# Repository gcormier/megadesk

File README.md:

# megadesk
Do you wish your IKEA Bekant had memory buttons? I sure did. So I made megadesk. Design goals were to have it fit in the original housing and use as many stock parts as possible, be completely independant of the existing controller, as well as store any number of memory positions.

You can now use the [megadesk companion](https://www.tindie.com/products/gcormier/megadesk-companion/) if you want to integrate it with your smarthome.

# For sale on Tindie - Plug and Play!
I've setup a store on Tindie for those who wish to order a ready to go, plug and play version. It comes with a fully assembled PCB as well as the cable you will need to connect it. No soldering or assembly required! <a  href="https://www.tindie.com/products/gcormier/megadesk/">https://www.tindie.com/products/gcormier/megadesk/</a>

## Features

### Recalibration
The factory recalibration routine has been implemented. The original BEKANT controller is no longer needed to recalibrate motors.
**This will cause the desk to move to the lowest possible extremity. Please exercise caution and be prepared to unplug the power if needed.**
Any interruption to this procedure requires a power-cycle.

### Serial control 
Enables serial input/output for what the megadesk is doing and to send commands. Some people wanted to have a smart/connected megadesk, but due to the size limitations of the space inside the case, an external module is the best solution. A lot of discussion in PR #12 and PR #58, as well as [discussion thread #87](https://github.com/gcormier/megadesk/discussions/87). 

You should also check out [Megadesk Companion](https://github.com/gcormier/megadesk_companion) for a plug and play `esphome` solution.

More information in [Serial.md](Serial.md). There's also specific details on [esphome](esphome.md).

### Custom MIN/MAX
Enabled by default, no limits.

This allows you to specify custom values for the minimum and maximum height of your desk. This is useful if you have things stored underneath, or maximum height limitations (shelf on the wall).

- Memory 11 will use the current desk height to set the minimum limit. If already set, it will clear it.
- Memory 12 will use the current desk height to set the maximum limit. If already set, it will clear it.

### Audio Feedback
Disabled by default.

Adds extra audio feedback when pushing buttons or using functions.

### Dual-button memory
Disabled by default.

This allows storing unique memory positions against each button. When enabled, you could save a double-click position for the up button as well a double-click position for the down button.

# Disassembly of the existing control unit
I now have a <a href="https://www.youtube.com/watch?v=jCPlM2KYwDQ">video with a few tips</a> on disassembling the IKEA Bekant controller and installing megadesk. Due to popular request, I now have a <a href="https://www.youtube.com/watch?v=qiOev3miDo8">second video with live surgery</a> of a brand new, unopened control unit.

**NOTE:** While the recalibration feature has been added to megadesk, it is recommended to keep your original board.

## Video
Unfortunately the beeps aren't captured well in the video unless you turn up the volume.

# Quick Commands
| UP pushes | Function | Audio Feedback
| --------- | -------- | --------
| 2-10      | Memory positions | # of beeps + high tone (saving), # of beeps (recall), # of beeps + sad tone (recall, no memory saved at that location)
| 11        | Set the lowest/minimum height to current position, or, reset back to default (toggles) | 4 low beeps when setting a limit. Single low beep - disabled.
| 12        | Set the highest/maximum height to current position, or, reset back to default (toggles) | 4 high beeps when setting a limit. Single high beep - disabled.
| 14        | Recalibration procedure, desk will lower down to the lowest limits | (Will begin moving)
| 15        | Reset | Fanfare
| 16        | Newer units, no operation. Units before Feb 2021 - toggle different variants.
| 17        | Toggle audio-feedback mode | double beep enabled. single beep disabled.
| 18        | Toggle both-button mode | double beep enabled. single beep disabled.

# Setting and Recalling memory slots
## Setting
To set assign a memory slot you press the up button two or more times. On the final button press you hold until you hear a tone that indicates what slot you have assigned (2 beeps, 3 beeps, etc).

## Recalling
To recall a memory slot you push the up button the number of times for that memory slot (2 for first slot, 3 for second slot, etc). If you try to recall a memory slot that has not been saved you will hear an "error" chime indicating that no height information could be recalled.

# Troubleshooting
1. Have you tried turning it off again? :)
    - Seriously - from testing many of these units, about 1 out of 20 times the handshake seems to fail as it does contain some random elements. A simple power cycle will provide a new handshake and the unit will power up.
    - Try unplugging the desk from the wall and plugging it back in (With megadesk connected)
    - Alternatively, try powering on the desk with NO controller attached, and then plugging in the megadesk after the desk is powered on.
    - Note that the power supply that comes with the BEKANT can store a charge for quite some time. It might be necessary to leave it unplugged for 60-120 seconds for it to lose that charge.
1. Is the safety key inserted? It is still required for the motors to engage. You will not hear any beeps when using buttons if it is removed.
1. Try different variant modes described above by pushing UP 16 times. (Pre Feb-2021 units only)
1. Test the buttons
    - Holding DOWN while powering on will wipe the EEPROM and enter a button test mode, where the up/down buttons can be held to test that they are working - a power cycle is required to exit this mode.
    - If they don't work
        - Ensure the safety key is fully inserted
        - Ensure the ribbon cable is seated far enough
        - If the FPC connector has a latch, ensure it is [latched](https://www.youtube.com/shorts/f_H-t_oJuzk)
        - You can clean the ribbon cable gently with a swab and rubbing alcohol which has been [reported to help](https://github.com/gcormier/megadesk/discussions/114) with intermittent issues
1. Factory Reset
    - Holding DOWN while powering on will wipe the EEPROM and enter a button test mode (see above) - a power cycle is required to exit this mode.
1. Recalibrate/reset the motors
   1. Factory controller
      - This step must be done with the **ORIGINAL** BEKANT controller.
      - Hold the UP and DOWN buttons for 8 seconds, after that let go of up while maintaining the pressure on the down button.
      - The desk will lower until it stops on its own.
      - Let go of all buttons, and test regular desk functionality with the original controller.
      - Once functionality is confirmed, replace with megadesk.   
   1. Megadesk
      - Push the UP button 14 times. 

# In the news
If you've made a blog/video posting with Megadesk, please open a PR to add it here, or send me a message with the URL.
1. https://calvin.me/ikea-bekant-megadesk/
1. https://www.youtube.com/watch?v=QopaeB1k6LU

# Hacking, contributing and DIY
This has been moved to [DIY.md](DIY.md) 

# esphome configuration
esphome example configuration avalible at [esphome.md](esphome.md), and other sample configurations in [esphome folder](https://github.com/gcormier/megadesk/tree/master/esphome)

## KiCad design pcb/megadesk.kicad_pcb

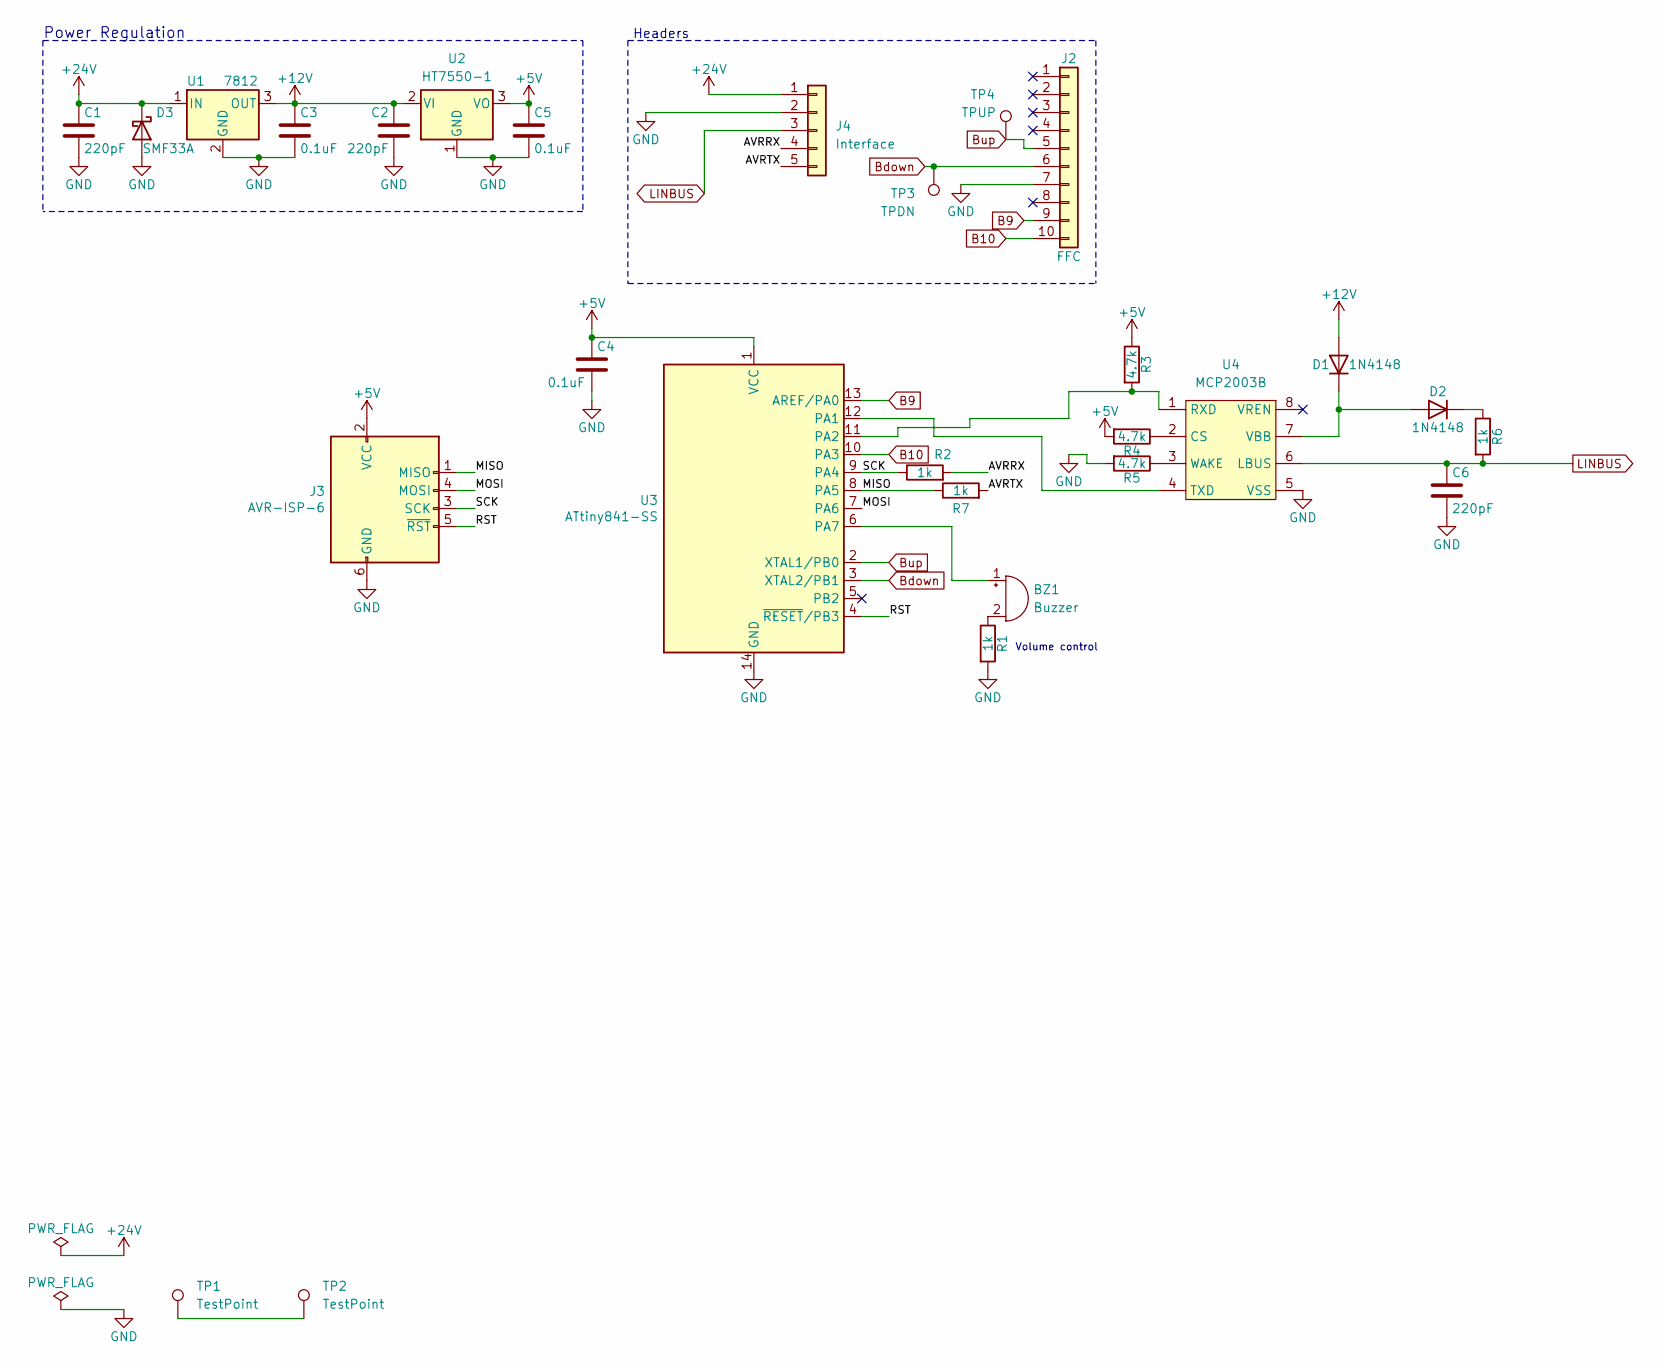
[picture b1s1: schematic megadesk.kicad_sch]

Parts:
BZ1: Buzzer; Buzzer_Murata_PKMCS0909E; Part Number PKMCS0909E4000-R1; LCSC C391035
C1, C2, C6: 220pF; C_0603_1608Metric; LCSC C1603
C3, C4, C5: 0.1uF; C_0805_2012Metric; LCSC C49678
D1, D2: 1N4148; D_SOD-323; Part Number 1N4148WSFSCT; LCSC C2128
D3: SMF33A; D_SOD-123F; LCSC C353288
J2: FFC; F1004-H-10-20G-R; Part Number A100308TR-ND; LCSC C668117
J3: AVR-ISP-6; PinHeader_2x03_P2.54mm_Vertical; Part Number DNP; LCSC DNP
J4: Interface; PinHeader_1x05_P2.54mm_Horizontal; LCSC C492413
R1, R2, R6, R7: 1k; R_0603_1608Metric; LCSC C21190
R3, R4, R5: 4.7k; R_0603_1608Metric; LCSC C23162
TP1, TP2: TestPoint; TestPoint_Pad_D1.5mm
TP3: TPDN; TestPoint_Pad_D1.5mm
TP4: TPUP; TestPoint_Pad_D1.5mm
U1: 7812; TO-252-2; Part Number 7812; LCSC C116325
U2: HT7550-1; SOT-89-3; LCSC C16106
U3: ATtiny841-SS; SOIC-14_3.9x8.7mm_P1.27mm; Part Number ATTINY841-SSUR; LCSC C614879
U4: MCP2003B; SOIC-8_3.9x4.9mm_P1.27mm; LCSC C152207

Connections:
+5V: C4.1, C5.1, J3.2 (VCC), R3.1, R4.2, U2.3 (VO), U3.1 (VCC)
+12V: C2.1, C3.1, D1.2 (A), U1.3 (OUT), U2.2 (VI)
+24V: C1.1, D3.1 (K), J4.1, U1.1 (IN)
/AVRRX: J4.4, R2.2
/AVRTX: J4.5, R7.2
/MISO: J3.1 (MISO), R7.1, U3.8 (PA5)
/MOSI: J3.4 (MOSI), U3.7 (PA6)
/RST: J3.5 (~RST), U3.4 (~RESET/PB3)
/SCK: J3.3 (SCK), R2.1, U3.9 (PA4)
B9: J2.9, U3.13 (AREF/PA0)
B10: J2.10, U3.10 (PA3)
Bdown: J2.6, TP3.1, U3.3 (XTAL2/PB1)
Bup: J2.5, TP4.1, U3.2 (XTAL1/PB0)
GND: C1.2, C2.2, C3.2, C4.2, C5.2, C6.2, D3.2 (A), J2.7, J3.6 (GND), J4.2, R1.2, R5.2, U1.2 (GND), U2.1 (GND), U3.14 (GND), U4.5 (VSS)
LINBUS: C6.1, J4.3, R6.2, U4.6 (LBUS)
unnamed: BZ1.2 (+), R1.1
unnamed: BZ1.1 (-), U3.6 (PA7)
unnamed: D1.1 (K), D2.2 (A), U4.7 (VBB)
unnamed: D2.1 (K), R6.1
unnamed: TP1.1, TP2.1
unnamed: U3.12 (PA1), U4.4 (TXD)
unnamed: R3.2, U3.11 (PA2), U4.1 (RXD)
unnamed: R4.1, U4.2 (CS)
unnamed: R5.1, U4.3 (WAKE)

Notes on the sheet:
Power Regulation
Headers
Volume control

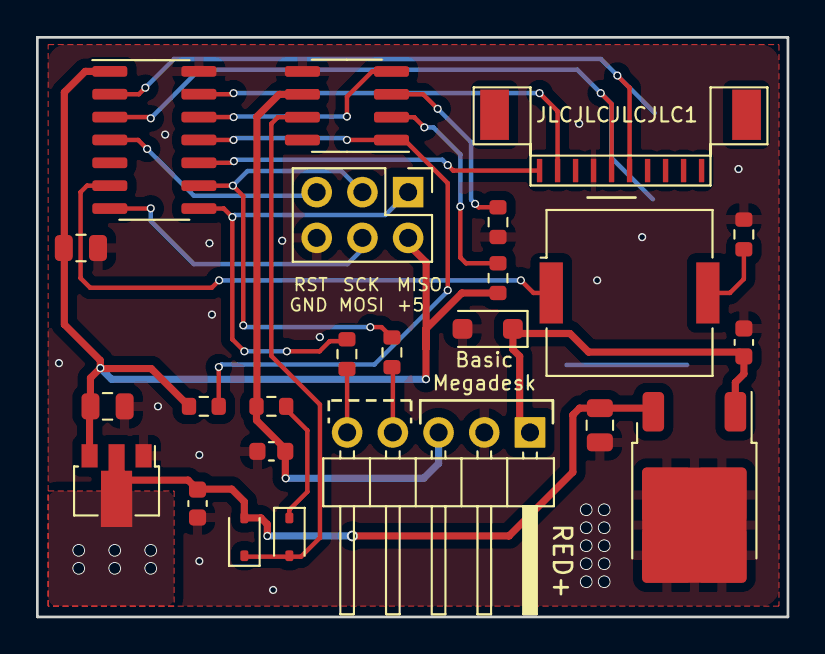
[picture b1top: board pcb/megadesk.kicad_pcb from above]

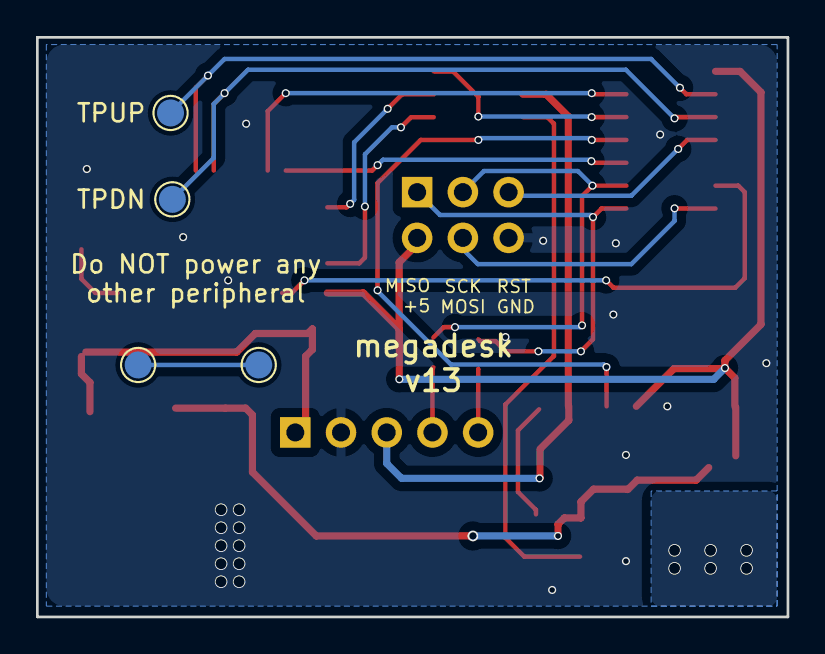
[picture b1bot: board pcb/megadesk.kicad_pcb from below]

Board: 2 copper layers, 41.7 x 32.2 mm, 28 parts (4 on the bottom side), 24 nets.

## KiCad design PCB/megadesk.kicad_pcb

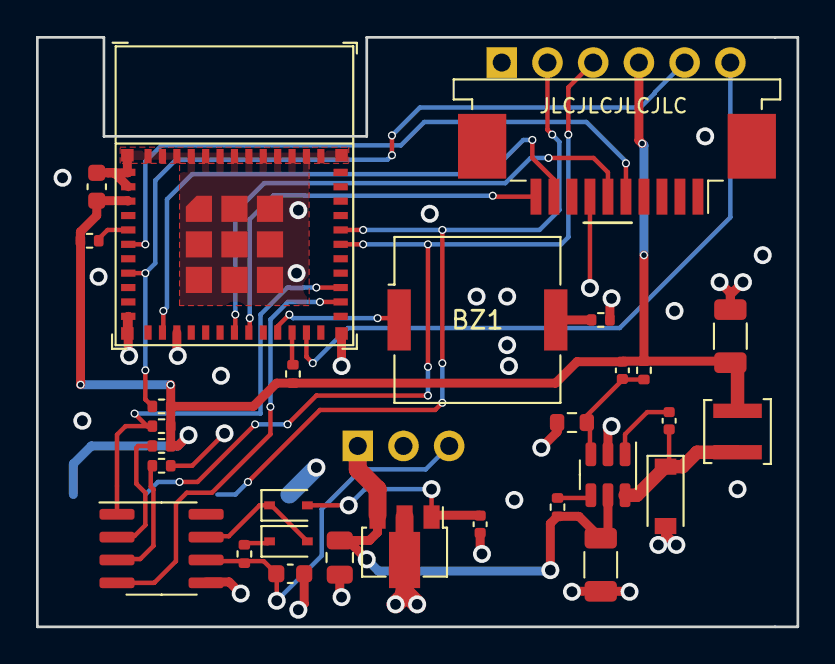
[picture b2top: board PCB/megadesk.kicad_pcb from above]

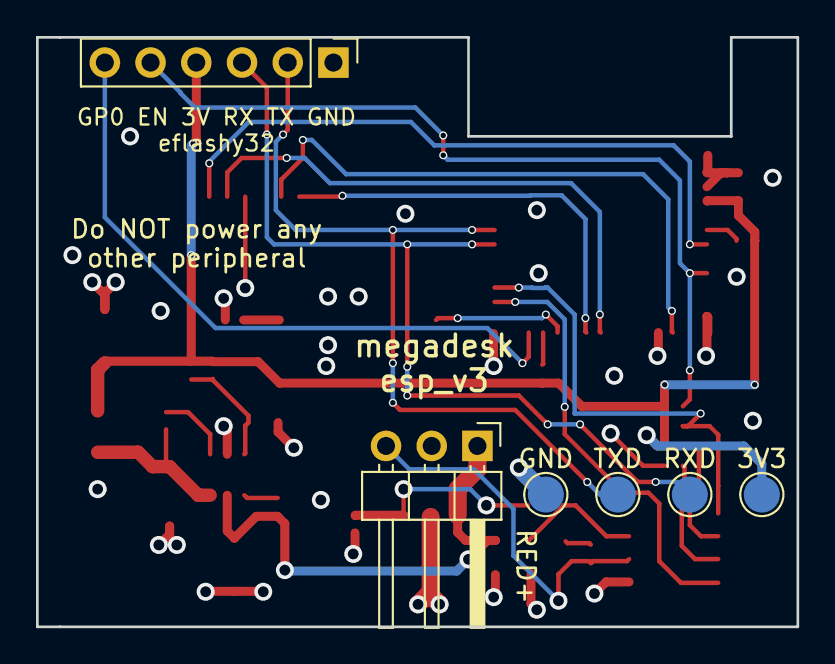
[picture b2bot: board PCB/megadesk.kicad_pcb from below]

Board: 4 copper layers, 42.2 x 32.8 mm, 35 parts (6 on the bottom side), 27 nets.

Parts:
BZ1: Buzzer; Buzzer_Murata_PKMCS0909E
C1: 0.33uF; C_0805_2012Metric
C3: 0.1uF; C_0402_1005Metric
C4: 10uF; C_0603_1608Metric
C6: 220pF; C_0603_1608Metric
C7: 4.7uF (50V); C_1206_3216Metric
C8: 0.1uF (50V); C_0402_1005Metric
C9: 33pF; C_0402_1005Metric
C10: 10uF (50V); C_1206_3216Metric
D1, D2: 1N4148; D_SOD-323
D4: 40V/1A; D_SOD-123
J1: Interface; PinHeader_1x03_P2.54mm_Horizontal
J2: FFC; TE_1-84953-0_1x10-1MP_P1.0mm_Horizontal
J3: eflashy32; PinHeader_1x06_P2.54mm_Vertical
L2: 2.2uH; L_Sunlord_SWPA3015S
R1, R6, R8: 1k; R_0402_1005Metric
R2, R7, R11: 10k; R_0402_1005Metric
R3, R4, R5: 4.7k; R_0402_1005Metric
R9: 40.2k; R_0603_1608Metric
R10: 124k; R_0402_1005Metric
TP1: RXD; TestPoint_Pad_D2.0mm
TP2: TXD; TestPoint_Pad_D2.0mm
TP3: GND; TestPoint_Pad_D2.0mm
TP4: 3V3; TestPoint_Pad_D2.0mm
U1: L78L12_SOT89; SOT-89-3
U2: ESP32-C3-MINI-1
U3: BL9342 / MP2451; SOT-23-6
U4: MCP2003B; SOIC-8_3.9x4.9mm_P1.27mm

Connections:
+3V3: C4.2, C9.2, C10.1, J3.4, L2.2, R2.1, R3.1, R4.2, R7.1, R10.2, R11.1, TP4.1, U2.3 (VDD)
+12V: C3.1, D1.2 (A), U1.1 (OUT)
+24V: C1.1, C7.2, J1.1, R8.1, U1.3 (IN), U3.5 (VIN)
/BOOT: C8.1, U3.1 (BOOT)
/EN: J3.5, R2.2, U2.8 (EN)
/FB: C9.1, R9.2, R10.1, U3.3 (FB)
/GPIO0: J3.6, U2.23 (IO9)
/PROGRXD: J3.3, TP1.1, U2.30 (IO20/RXD)
/PROGTXD: J3.2, TP2.1, U2.31 (IO21/TXD)
/RXD: R3.2, U2.27 (IO19/D+), U4.1 (RXD)
/SW: C8.2, D4.1 (K), L2.1, U3.6 (SW)
/SWEN: R8.2, U3.4 (EN)
/TXD: U2.26 (IO18/D-), U4.4 (TXD)
B9: J2.9, U2.13 (IO1)
B10: J2.10, U2.19 (IO5)
Bdown: J2.6, U2.18 (IO4)
Bup: J2.5, U2.6 (IO3)
GND: C1.2, C3.2, C4.1, C6.2, C7.1, C10.2, D4.2 (A), J1.2, J2.7, J3.1, R1.2, R5.2, R9.1, TP3.1, U1.2 (GND), U2.1 (GND), U2.2 (GND), U2.11 (GND), U2.14 (GND), U2.36 (GND), U3.2 (GND), U4.5 (VSS)
LINBUS: C6.1, J1.3, R6.2, U4.6 (LBUS)
unnamed: BZ1.1 (-), U2.21 (IO7)
unnamed: BZ1.2 (+), R1.1
unnamed: D1.1 (K), D2.2 (A), U4.7 (VBB)
unnamed: D2.1 (K), R6.1
unnamed: R4.1, U4.2 (CS)
unnamed: R5.1, U4.3 (WAKE)
unnamed: R7.2, U2.5 (IO2)
unnamed: R11.2, U2.22 (IO8)

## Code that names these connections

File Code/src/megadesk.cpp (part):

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#define MOVE_OFFSET   159    // amount to move when moving manually

#ifdef AVR2
  #define PIN_UP          PIN_PA5
  #define PIN_DOWN        PIN_PA6
  #define PIN_BEEP        PIN_PA7
  #define PIN_LIN_SERIAL  PIN_PA1
  
  HardwareSerial &userSerial = Serial;
  HardwareSerial &linSerial = Serial1;

#else
  #define PIN_UP          PIN_PB0
  #define PIN_DOWN        PIN_PB1
  #define PIN_BEEP        PIN_PA7
  #define PIN_LIN_SERIAL  PIN_PA1

  HardwareSerial &userSerial = Serial1;
  HardwareSerial &linSerial = Serial;
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
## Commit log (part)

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2019-02-04 fix pic size
2019-03-03 fix large variant instructions
2019-04-11 youtube url
2019-04-11 Updated a few things and clean up some backup files.
2019-04-11 another gitignore
2019-11-02 Single sided revision for easier assembly in reflow oven.
2019-11-15 Include interactive BOM
2019-11-15 update ignore
2019-11-15 updates for v4
2019-11-15 front image only for v4
2019-12-15 Clean up a bit of silkscreen
2019-12-20 change to platformIO
2019-12-20 remove whitespace
2019-12-20 remove unused function
2020-04-04 Fixes #22 and add all fuses explicitly
2020-04-05 Should fix overshoot
2020-04-05 variant updates
2020-04-05 simple hysteresis increase to handle overshoot
2020-05-24 adding readme notes
2020-05-24 notes and programming header picture
2020-05-24 image resize and partnumber
2020-07-06 Add Martela S&S Rol Ergo table LIN Bus recordings and specs
2020-07-10 update readme with new troubleshooting section
2020-07-10 more troubleshooting
2020-07-16 discount
2020-11-14 disassembly video
2020-11-29 kits no longer offered
2020-12-05 formatting
2021-01-09 more serial work and add header declarations
2021-01-10 more serial work (8192 out of 8192 bytes)
2021-01-10 minor formating
2021-01-23 Multiple fixes and renames. Most serial functions work.
2021-01-24 EEPROM serial functions now work
2021-01-24 update serial structure comment
2021-01-24 memory reduction
2021-01-24 add windows/pololu programmer target
2021-01-24 change all uint8_t to byte for consistancy
2021-01-24 change button presses from `int` to `uint8_t`
2021-01-24 change recvInProgress from `bool` to `uint8_t` to save 10 bytes
2021-01-26 Added custom MIN/MAX and compile #DEFINE options for SERIALCOMMS and MINMAX
2021-01-27 update to documents, new video
2021-01-27 v6 notes
2021-02-08 Simplify Min/Max optioning without size change
2021-02-08 Add BusPirate upload config
2021-02-08 change buttom movements to absolute value serial output
2021-02-09 updated command_read and command_write
    command_read bits were swapped
    command_write optomized and now updates min/max height when saved
2021-02-09 Add "do not discard" warning to README.md
    Might save someone else some future pain and suffering
2021-02-15 fix min/max height load and manual move w/serial
    minHeight and maxHeight boot load fixed
    currently min/max cannot use with serial enabled because of space constraints
    manual move fixed, now reports change betewwn last value and current value
    may still be off by some on last loop
2021-02-16 Serial: print height after manual move finished
2021-02-18 allow min/max and manual move upades w/more memory
    If flash space is more than 8k then allow manual move continuous updates with min/max height
2021-02-23 adding 3rd variant for #46, need to test
2021-02-23 update readme with notes as per #46
2021-03-02 add buspirate programmer
2021-03-02 add serial and minmax
2021-04-30 setting and recalling memory slots
    Add section with instructions on setting and recalling memory slots.
2021-05-21 more tuneful + save 10bytes
2021-05-23 fewer globals. defines. avoid casts.
2021-05-23 Adjust readme to reflect software versions better
2021-05-23 lean 16bit eeprom functions
2021-05-23 tone took >800b of flash. heres a leaner alternative
2021-05-23 no need for 2 lin::send() when 1 will do
2021-05-24 clarifications and cleanups. move globals to local
2021-05-25 both button memories
2021-05-25 descriptive names. follow naming convention. use enum Class to save some flash
2021-05-26 more descriptive
2021-05-26 even leaner tone generation
2021-05-26 update documentation for both-button operations
2021-05-26 remove minmax conditional code in serialcomms
2021-05-26 recalibration routine
2021-05-27 ditch safety margin after some testing
2021-05-27 DOWN factory reset and button test
2021-05-27 reduce startup delay
2021-05-27 fix playTone to play the freqency requested, and use lower octave sounds
2021-05-28 easter!
2021-05-28 Fix sudden stop when going up
2021-05-29 make 1s tones possible. add DIY cable pic.
2021-05-29 Update DIY.md
    fix cable picture reference
2021-05-29 better clarify cable options. layout change.
2021-05-29 better layout
2021-05-31 mention right angle header
2021-05-31 nothing much
2021-06-01 #define for feedback feature
2021-06-04 Quick Commands table
2021-06-04 easter savings. feedback fix
2021-06-04 rework serial
2021-06-04 add tone to serial commands
2021-06-05 avoid action when currentHeight=0. other protection on targetHeight
2021-06-05 full Tx/Rx human-serial. fixes for bothbutton load command support
2021-06-11 tidy, comments, refactor slightly
2021-06-11 serial cmds: sl. serial errors.
2021-06-11 serial commands and example output. start of a sanity test-suite
2021-06-12 space savings via some button handling refactoring
2021-06-12 ensure we exit recalibration if motors bottom-out @ position <99
2021-06-12 Allow manual button control if out-of-bounds.
2021-06-15 eliminate proto=1 code. remove SerialOn
2021-06-15 some more savings
2021-06-16 fix eeprom erase hang
2021-06-19 use uint8 for erasing eeprom
2021-06-20 function-static arrays save flash
2021-06-25 Implement a watchdog software-reset
2021-06-25 5 presses to reset, even if lin is down
2021-06-25 better shell-monitor defaults
2021-06-25 DEBUGSTARTUP #define
2021-06-25 smaller linInit() implementation
2021-06-26 refactored (smaller) Lin send/recv
2021-06-27 timeout was 17360us. corrected to 12916us
2021-06-27 diagnostic frames checksum consolidation
2021-06-27 tighten delay_until usage. use before time-sensitive operations
2021-06-28 delaying 6ms in linBurst() avoids delayUntil() reporting its late
2021-06-28 improve comments. timeoutCount->countDown
2021-06-29 optimize for speed instead of space - revert to 5ms intervals in linBurst()
2021-07-01 better raw display packets when using DEBUGSTARTUP. first byte is length
2021-07-01 small tidy, revert to sensible serial options
2021-07-01 ENABLERESET #def to enable/disable soft-reset
2021-07-20 megaupdate
2021-07-22 some documentation clarifications/fixes
2021-07-22 move force reset to position 10
2021-07-25 Fix recv checksum. use human serial monitor settings by default
2021-07-25 remove commented code
2021-07-25 document reset on slot 15
2021-07-26 add pololu linux build environment
2021-07-26 don't use drift if serial isn't defined
2021-07-26 fix reset slot 15
2021-07-26 more formatting/indentation
2021-08-15 abort linBurst() if motor response times-out
2021-08-18 optimize image size some more
2021-08-22 state machine tidy. use enc max/min.
2021-08-22 SERIALHEIGHT telemetry
2021-08-23 Ignore mismatched idles. fixes manual button failures?
2021-08-23 tidy + comments
2021-08-24 tidy, turn off debug serial options
2021-09-12 disable serial in main build
2021-11-10 PCB revision v7
2021-12-03 add kibot file
2022-01-30 change some footprints to new libraries, add ffc alternative
2022-02-17 automation
2022-02-17 pcb revision only
2022-02-17 fix branch name for automation
2022-03-01 build environments dedicated to GH actions
2022-03-20 serial/esphome documentation
2022-03-20 typo
2022-03-20 more typos
2022-03-20 pcb release action
2022-03-20 fix folder
2022-03-21 - Added epshome sliders for desk height in Inches, CM, and raw - Custom componet required to interpret the received data - Changed switches to buttons - Added buttons for commands 11, 12, 14, 15, 17,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
2022-03-21 Moved serial info to separate file
2022-03-21 - Move epshome example to a seperate file - changed esphome height range to verified heights
2022-03-22 fixed code formatting and added image
2022-03-22 Add Home-Assistant.jpg and fix esphome.md
2022-03-24 Update Serial.md
    further adjustments
2022-08-18 1624 pio and comment out broken reset for now
2022-08-18 push action run on all branches
2022-08-18 Update to 1624 (v9)
2022-08-18 Hide U3 silkscreen
2022-08-18 move header title
2022-08-29 1624 specific
2022-08-30 Seperate serials, fix reset
2022-08-30 notes
2022-09-01 esp32c3mini
2022-09-06 force pinMode() for serialBreak
2022-09-09 Serial
2022-09-10 eeprom clear based on reported size
2022-09-10 boundary
2022-09-10 redefine pins, fix reset for t841
2022-09-10 update serial default no
2022-09-10 builds for actions
2022-09-10 update actions for builds
2022-09-10 actions
2022-09-10 fix duplicate build flags
2022-09-10 axtion
2022-09-10 basefilename
2022-09-10 filez
2022-09-10 filez2
2022-09-10 make build folder
2022-09-10 renames
2022-09-10 add manual dispatch
2022-09-10 grab gh actions files
2022-09-10 push version conditional
2022-09-10 rename
2022-09-10 rename workflow
2022-09-10 duplicate version action
2022-09-10 fix fab actions
2022-09-10 copy master actions
2022-09-22 fix serial build config
2022-09-23 move variants info to seperate file
2022-09-23 touch up main readme
2022-09-23 wordsmith
2022-10-03 Update esphome.md
    Added a space after baud_rate: to resolve configuration error. Also added link to help for those not using the d1_mini board, changed wifi to use best practices (secrets) and a comment on the ESPHome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
2022-10-13 esp rev2
2022-10-13 actions tweak
2022-10-13 move origin for jlc bug
2022-11-13 add esphome contribution
2022-11-13 comment yaml
2022-11-13 move folder
2022-11-13 button cover
2022-11-15 actions updates
2022-11-15 action upgrade
2022-11-15 remove echo
2022-11-17 add esp build
2022-11-18 refactor
2022-11-19 ugh v3
2022-12-01 change folder case
2022-12-21 action changes
2022-12-21 buzzer stp
2022-12-21 firmware build status
2022-12-21 size
2022-12-21 update versions
2022-12-21 serial enable
2023-02-25 simplify caps
2023-02-26 panels
2023-02-26 duplicate name
2023-02-26 panel fab
2023-02-26 fixy
2023-02-26 fix root ownership
2023-02-26 weee
2023-02-26 change panel opts
2023-02-26 tweak
2023-02-26 try to use templated job
2023-03-06 ugh. fix bad pins.
2023-03-08 4hole
2023-03-08 vcut layer
2023-03-08 diff layer
2023-03-08 again
2023-03-08 edgecuts
2023-03-08 more panel
2023-03-10 temp 2x3 for test
2023-03-10 back to 5x4
2023-03-16 kicad v7
2023-03-21 fix silkscreen kibot and v7
2023-03-22 2 rows only for testing
2023-03-22 back to 4
2023-03-22 update PN for header
2023-03-22 fix tags
2023-04-01 esphome powershell sample
2023-04-03 Update readme.md
    - Added missing backslashing in windows path so github renders them correctly for displaying
    - Fixed some typos
2023-04-03 Some improvements in the readme.md (#131)
    * Update readme.md
    - Added missing backslashing in windows path so github renders them correctly for displaying
    - Fixed some typos
    * Update readme.md
2023-04-23 allow desk to move sometimes when out of bounds
2023-04-29 add PN's for ic
2023-04-29 update panel regex
2023-04-29 include 3-pin in POS
2023-04-29 include non-smd in position
2023-04-29 update PN
2023-05-15 refillzones
2023-05-22 5pin ver
2023-05-26 5pin version
2023-05-26 update v12 5pin
2023-05-27 add secrets sample
2023-05-27 ignore secrets
2023-05-27 ignore update
2023-05-27 move uart up and add comments
2023-05-27 more notes
2023-05-27 add companion yaml
2023-06-09 Update megadesk-companion.yaml
    esp32-c3 support has been added only last year to arduino/espressif32. Doesn't seem to run with older versions. Added the most recent versions to the yaml to make avoid running into version issues/co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
2023-06-11 add comment about version
2023-06-11 format
2023-07-04 companion note
2023-08-08 readme
2023-08-09 test board
2023-08-09 change rows to 1 for testing
2023-08-09 4 layer!
2023-08-12 Don't need these anymore
2023-08-12 cleanup
2023-08-13 FPC adjustment, 2 resistors for RP protection
2023-08-19 gitignore
2023-10-08 pipeline changes
2023-10-08 more panel changes
2023-11-01 use espidf and comments
2023-12-14 idf stuff
2024-01-15 silkscreen change
2024-01-15 dev pipeline
2024-01-24 rename files and make it clearer
2024-05-04 Moved 5pos header to make reassembly easier, better footprint for ribbon connector compatibility, rounded PCB edges, slight increase in width (too sloppy)
2024-05-04 Updated render
2024-07-09 update config for new esphome version
2024-07-10 Updates fuses for BOD
2024-07-16 fix up fuses
2024-07-31 decoupling
2024-07-31 ignore cache
2024-09-01 no more dev action
